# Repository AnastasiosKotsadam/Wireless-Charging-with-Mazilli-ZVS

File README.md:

# ZVS Driver with Protection

A **Mazzilli ZVS (zero-voltage switching) driver** for wireless energy transfer, built as a complete PCB with hardware overcurrent protection and an ATmega328P supervisor that monitors the oscillation, controls the startup and shows the board status on LEDs.

> **Status:** simulation (LTspice) and firmware (SimulIDE) done · schematic in KiCad in progress · PCB not yet built

---

## Features

- **Mazzilli ZVS power stage** at about **111 kHz**, powered from a **12 V DC** input
- **Soft start** that holds the MOSFET gates off at power-up
- **Hardware overcurrent protection**: shunt → current-sense amplifier → comparator → latch → gates off within microseconds, independent of the firmware
- **Two current limits** set by the ATmega: a high limit during startup (to allow the inrush current) and a normal limit during operation
- **Oscillation watchdog**: the ATmega counts the drain pulses and shuts the stage down if the frequency is missing or outside its window
- **Fault diagnosis on LEDs**: overcurrent and oscillation faults are shown separately
- **Safe by default**: the latch starts in the "off" state at power-up and after any fault, and only a button press restarts the stage

---

## How it works

```
12 V ─ Fuse ─ Shunt (5 mΩ) ─ Soft start ─ Mazzilli ZVS ─ Coupled coils ─ Rectifier ─ Load
                  │                            ▲      │
             INA181A1 (×20)                    │      │ drain signal
                  │                      gates off    │ (divider, clamp, Schmitt trigger)
             RC filter                         │      ▼
                  │                     ┌─ Fault latch ◄─── ATmega328P
             LM393 comparator ──────────┘  (74HC02)        - threshold PWM
                  ▲                                        - frequency watchdog
                  └──── threshold (PWM + RC filter) ◄──────  - LEDs, reset button
```

1. **Overcurrent:** the INA181 amplifies the voltage across the shunt. When it exceeds the threshold, the LM393 sets the latch, and two small MOSFETs pull both main gates to ground.
2. **Oscillation watchdog:** one drain is divided down, clamped and cleaned up by a Schmitt trigger, then counted by Timer1 of the ATmega. A missing or wrong frequency makes the ATmega set the latch.
3. **Startup:** the ATmega first sets the high threshold, waits for it to settle, then resets the latch. After a blanking time and a valid frequency, it switches to the normal threshold.

---

## Key parameters

| Parameter | Value |
|---|---|
| Input voltage | 12 V DC |
| Switching frequency | ~111 kHz (tank: 2 µH, 1 µF) |
| Feed chokes | 2 × 100 µH |
| Shunt | 5 mΩ |
| Current-sense amplifier | INA181A1 (gain 20, 0.1 V/A) |
| Trip current, startup | 30 A (first ~30 ms) |
| Trip current, running | 8 A |
| Frequency window | 90–130 kHz (to be confirmed by measurement) |
| Comparator | LM393, supplied from 12 V, open-collector output |
| Fault latch | 74HC02 (two NOR gates as SR latch) |
| Microcontroller | ATmega328P-PU, 16 MHz crystal, 5 V |
| Logic supply | 7805 linear regulator |

---

## LED indication

| LEDs | State |
|---|---|
| All off | Booting |
| 🟢 Green blinking | Startup, high current limit active |
| 🟢 Green steady | Running normally |
| 🔴 Red | Overcurrent trip |
| 🟡 Yellow | Oscillation fault (missing or wrong frequency) |

After a fault, the stage stays off until the **reset button** is pressed.

---

## Repository structure

```
ZVS-Driver/
├── kicad/        KiCad schematic and PCB
├── ltspice/      LTspice simulations (power stage, protection, coupling sweeps)
├── firmware/
│   └── zvs_supervisor/
│       └── zvs_supervisor.ino
├── docs/         Notes, measurements, photos
└── README.md
```

---

## Firmware

**Toolchain:** Arduino IDE 2.x with the [MiniCore](https://github.com/MCUdude/MiniCore) board package.

| Setting | Value |
|---|---|
| Board | MiniCore → ATmega328 |
| Clock | External 16 MHz |
| BOD | 4.3 V |
| Bootloader | No bootloader (programmed via ISP) |
| Programmer | Arduino as ISP |

The same code also runs unchanged on an Arduino Uno or Nano for testing.

### Pin map

| Arduino | ATmega pin | Function |
|---|---|---|
| D2 | 4 | Reset button (to GND) |
| D3 | 5 | Threshold PWM (Timer2, ~31 kHz) |
| D5 | 11 | Oscillation input (Timer1, T1) |
| D6 | 12 | Latch S (via 1N5819) |
| D7 | 13 | Latch R |
| D8 | 14 | Latch Q (read back) |
| A0 / A1 / A2 | 23 / 24 / 25 | Green / red / yellow LED |
| A3 | 26 | Current-sense output (debug) |
| D0 / D1 | 2 / 3 | Serial debug, 115200 baud |

All thresholds, timings and the frequency window are constants at the top of `zvs_supervisor.ino`.

### Programming

The board has a 6-pin ISP header (MISO, VCC, SCK, MOSI, RESET, GND). An Arduino Uno running the **ArduinoISP** example works as programmer (D10 → RESET, D11 → MOSI, D12 → MISO, D13 → SCK, plus 5 V and GND, and 10 µF between RESET and GND on the Uno).

1. Burn the fuses once: **Tools → Burn Bootloader**.
2. Upload: **Sketch → Upload Using Programmer**.

⚠️ **Program the board with the 12 V supply disconnected.** While the ATmega is being programmed it cannot supervise the power stage.

### Serial debug

A 3-pin header (GND, TX, RX) connects to a 5 V USB-UART adapter (CH340 or CP2102). TX and RX cross over, and the adapter's VCC stays unconnected.

---

## Simulation

- **LTspice:** power stage, soft start, current sensing, comparator, latch and drain sensing, with faults (shorted tank) and coupling-factor sweeps between the coils. The TI models for the INA181 and LM2903B/LM393 are available from [ti.com](https://www.ti.com) and are not included in this repository.
- **SimulIDE:** the ATmega328P running the compiled firmware, with LEDs, button, latch and a test signal on the oscillation input.

---

## Roadmap

- [x] Power stage and protection simulated in LTspice
- [x] Firmware written and tested in SimulIDE
- [ ] Finish KiCad schematic and run ERC
- [ ] Breadboard test of the control and protection circuit
- [ ] Perfboard test of the power stage with a current-limited supply
- [ ] PCB layout, revision A
- [ ] Measurements on the real board and tuning of the thresholds

---

## Safety

This circuit handles high currents, and the drain voltages reach several times the supply voltage. Test new hardware with a **current-limited lab supply**, start at low voltage, and never connect an oscilloscope ground clip to a drain. The coil and workpiece can get hot.

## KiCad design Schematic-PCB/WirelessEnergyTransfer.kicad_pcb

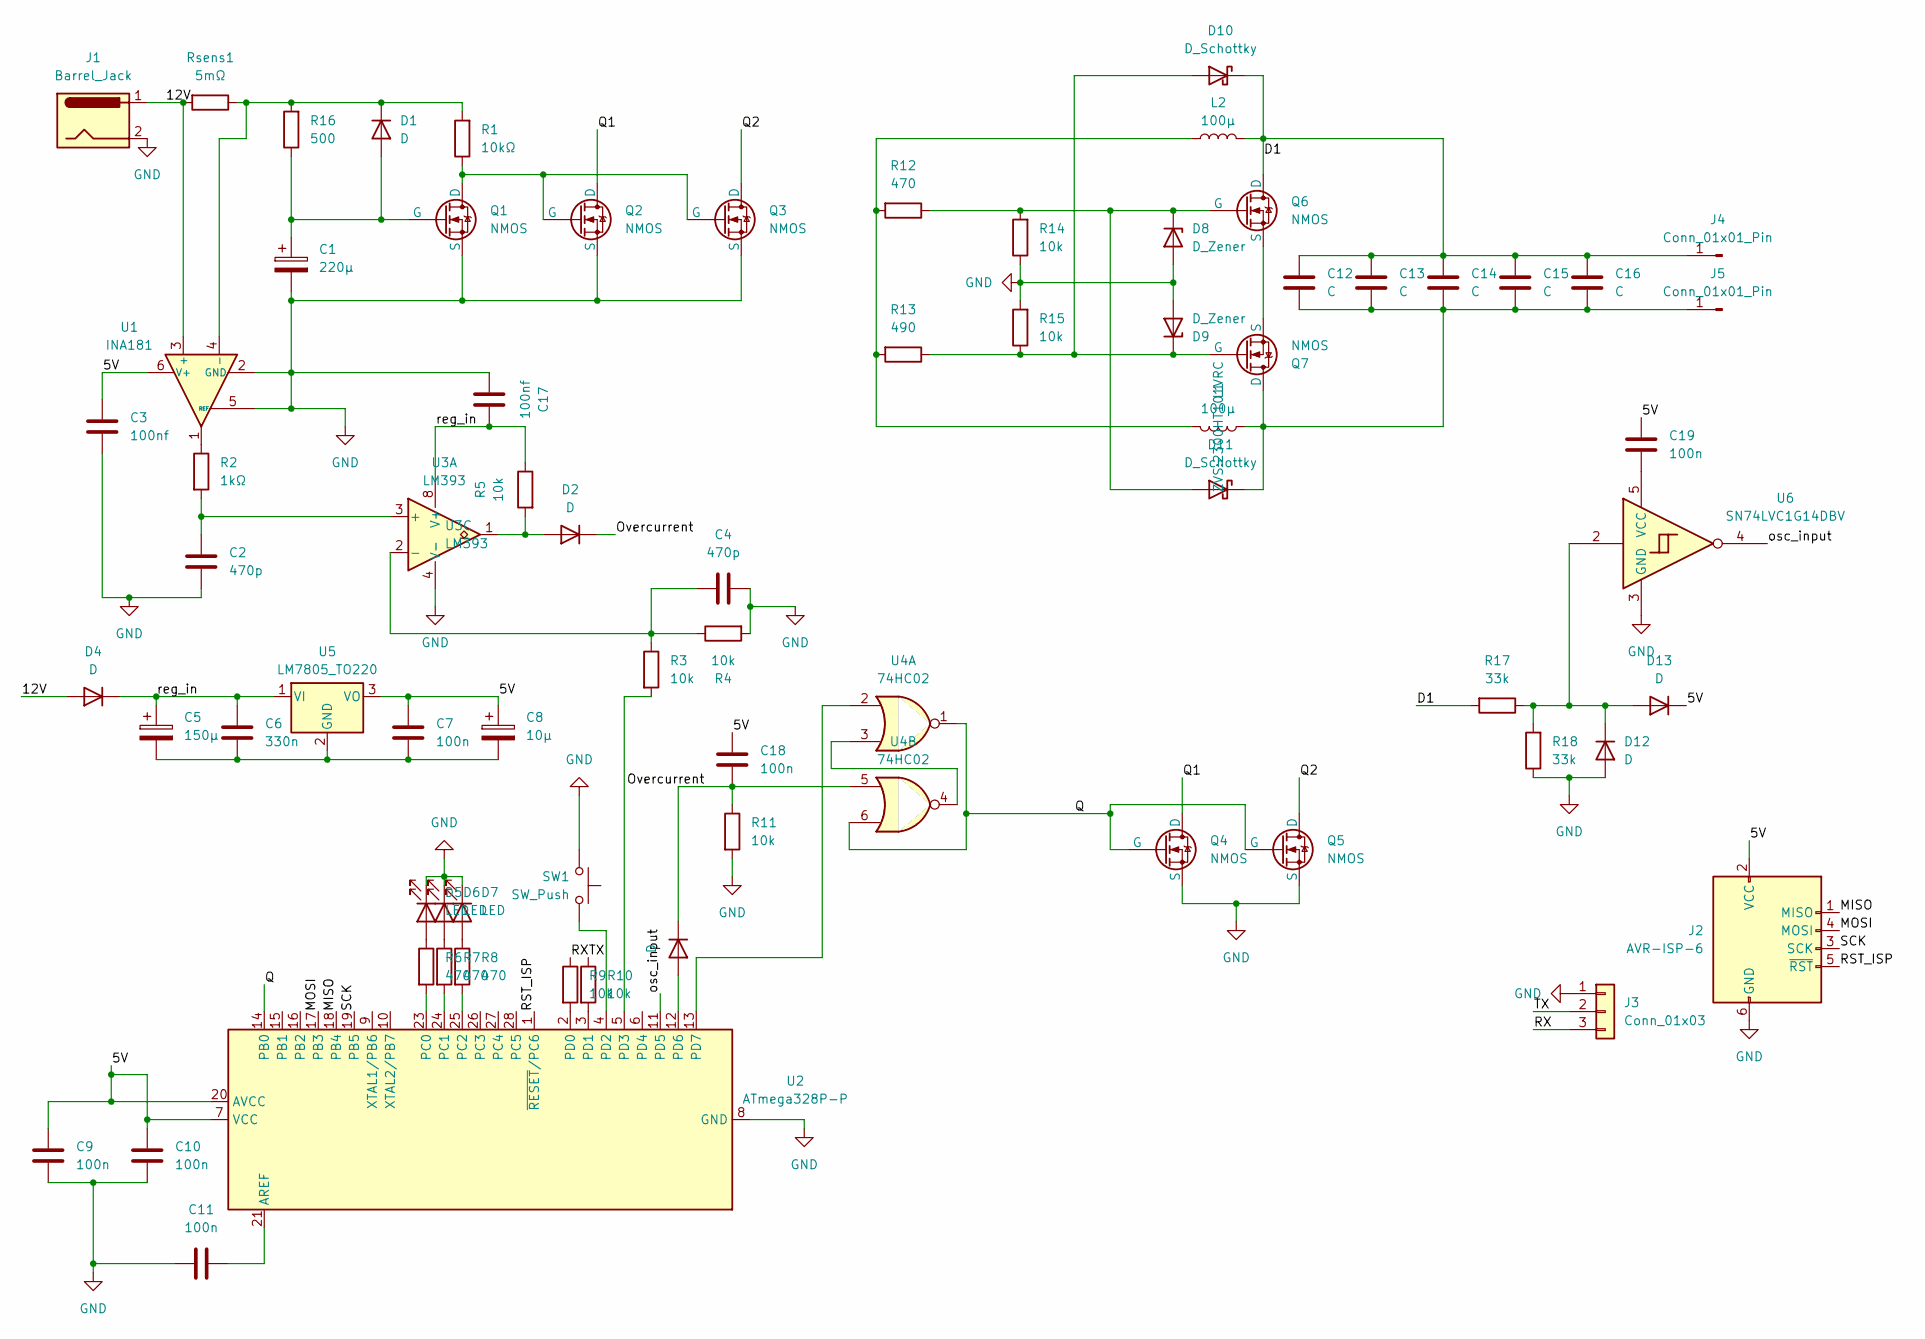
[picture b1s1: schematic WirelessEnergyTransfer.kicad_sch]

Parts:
C1: 220μ; CP_Radial_D10.0mm_P5.00mm
C2, C4: 470p; C_Axial_L5.1mm_D3.1mm_P7.50mm_Horizontal
C3, C17: 100nf; C_Disc_D10.0mm_W2.5mm_P5.00mm
C5: 150μ; CP_Radial_D10.0mm_P5.00mm
C6: 330n; C_Disc_D10.0mm_W2.5mm_P5.00mm
C7, C9, C10, C11, C18, C19: 100n; C_Disc_D10.0mm_W2.5mm_P5.00mm
C8: 10μ; CP_Radial_D10.0mm_P2.50mm_P5.00mm
C12, C13, C14, C15, C16: C; R76QR32204030J
D1, D4: D; DIOAD3020W130L900D530
D2, D3, D12, D13: D; D_DO-35_SOD27_P10.16mm_Horizontal
D5, D6, D7: LED; LED_D3.0mm_IRBlack
D8, D9: D_Zener; DIOAD1413W86L463D238
D10, D11: D_Schottky; DIOAD3020W130L900D530
J1: Barrel_Jack; BarrelJack_Horizontal
J2: AVR-ISP-6; IDC-Header_2x03_P2.54mm_Horizontal
J3: Conn_01x03; PinSocket_1x03_P2.54mm_Horizontal
J4, J5: Conn_01x01_Pin; TestPoint_Pad_4.0x4.0mm
L1, L2: 100μ; 2300HT101VRC
Q1, Q2, Q3, Q4, Q5: NMOS; 2N3904BU
Q6, Q7: NMOS; TO254P465X1028X1970-3P
R1: 10kΩ; R_Axial_DIN0309_L9.0mm_D3.2mm_P12.70mm_Horizontal
R2: 1kΩ; R_Axial_DIN0309_L9.0mm_D3.2mm_P12.70mm_Horizontal
R3, R4, R5, R9, R10, R11: 10k; R_Axial_DIN0309_L9.0mm_D3.2mm_P12.70mm_Horizontal
R6, R7, R8: 470; R_Axial_DIN0309_L9.0mm_D3.2mm_P12.70mm_Horizontal
R12: 470; R_Axial_DIN0411_L9.9mm_D3.6mm_P15.24mm_Horizontal
R13: 490; R_Axial_DIN0411_L9.9mm_D3.6mm_P15.24mm_Horizontal
R14, R15: 10k; R_Axial_DIN0411_L9.9mm_D3.6mm_P15.24mm_Horizontal
R16: 500; R_Axial_DIN0411_L9.9mm_D3.6mm_P15.24mm_Horizontal
R17, R18: 33k; R_Axial_DIN0309_L9.0mm_D3.2mm_P12.70mm_Horizontal
Rsens1: 5mΩ; R_Axial_DIN0411_L9.9mm_D3.6mm_P15.24mm_Horizontal
SW1: SW_Push; SW_CW_GPTS203211B
U1: INA181; SOT-23-6
U2: ATmega328P-P; DIP-28_W7.62mm
U3: LM393; PS8
U4: 74HC02; DIP-10_W7.62mm
U5: LM7805_TO220; TO-220-3_Vertical
U6: SN74LVC1G14DBV; SOT-23-5

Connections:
/5V: C3.1, C7.2, C8.1, C9.2, C10.2, C18.2, C19.2, D13.1 (K), J2.2 (VCC), U1.6 (V+), U2.7 (VCC), U2.20 (AVCC), U5.3 (VO)
/12V: D4.2 (A), J1.1, Rsens1.2, U1.3 (+)
/D1: C12.1, C13.1, C14.1, C15.1, C16.1, D10.1 (K), J4.1 (Pin_1_1), L2.1, Q6.1 (D), R17.2
/MISO: J2.1 (MISO), U2.18 (PB4)
/MOSI: J2.4 (MOSI), U2.17 (PB3)
/Overcurrent: C18.1, D2.1 (K), D3.1 (K), R11.1, U4.5
/Q: Q4.2 (G), Q5.2 (G), U2.14 (PB0), U4.1, U4.6
/Q1: Q2.1 (D), Q4.1 (D)
/Q2: Q3.1 (D), Q5.1 (D)
/RST_ISP: J2.5 (~RST), U2.1 (~RESET/PC6)
/RX: J3.3, R9.1
/SCK: J2.3 (SCK), U2.19 (PB5)
/TX: J3.2, R10.1
/osc_input: U2.11 (PD5), U6.4
/reg_in: C5.1, C6.2, C17.2, D4.1 (K), R5.1, U3.8 (V+), U5.1 (VI)
GND: C1.2, C2.1, C3.2, C4.1, C9.1, C10.1, C11.1, C17.1, D5.1 (K), D6.1 (K), D7.1 (K), D8.2 (A), D9.2 (A), D12.2 (A), J1.2, J2.6 (GND), J3.1, Q1.3 (S), Q2.3 (S), Q3.3 (S), Q4.3 (S), Q5.3 (S), R4.2, R11.2, R14.1, R15.2, R18.1, SW1.2, U1.2 (GND), U1.5 (REF), U2.8 (GND), U2.22 (GND), U3.4 (V-), U6.3 (GND)
unnamed: C1.1, D1.2 (A), Q1.2 (G), R16.1
unnamed: D1.1 (K), R1.2, R16.2, Rsens1.1, U1.4 (-)
unnamed: D2.2 (A), R5.2, U3.1
unnamed: D3.2 (A), U2.12 (PD6)
unnamed: D5.2 (A), R6.1
unnamed: D6.2 (A), R7.1
unnamed: D7.2 (A), R8.1
unnamed: D9.1 (K), D10.2 (A), Q7.2 (G), R13.1, R15.1
unnamed: D8.1 (K), D11.2 (A), Q6.2 (G), R12.1, R14.2
unnamed: C12.2, C13.2, C14.2, C15.2, C16.2, D11.1 (K), J5.1 (Pin_1_1), L1.1, Q7.1 (D)
unnamed: D12.1 (K), D13.2 (A), R17.1, R18.2, U6.2
unnamed: L1.2, L2.2, R12.2, R13.2
unnamed: Q1.1 (D), Q2.2 (G), Q3.2 (G), R1.1
unnamed: Q6.3 (S), Q7.3 (S)
unnamed: R2.1, U1.1
unnamed: C11.2, U2.21 (AREF)
unnamed: R6.2, U2.23 (PC0)
unnamed: R7.2, U2.24 (PC1)
unnamed: R8.2, U2.25 (PC2)
unnamed: R9.2, U2.2 (PD0)
unnamed: R10.2, U2.3 (PD1)
unnamed: SW1.1, U2.4 (PD2)
unnamed: R3.2, U2.5 (PD3)
unnamed: U2.13 (PD7), U4.2
unnamed: C2.2, R2.2, U3.3 (+)
unnamed: C4.2, R3.1, R4.1, U3.2 (-)
unnamed: U4.3, U4.4
unnamed: C5.2, C6.1, C7.1, C8.2, U5.2 (GND)
unnamed: C19.1, U6.5 (VCC)

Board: 2 copper layers, 72 parts (0 on the bottom side), 45 nets, no tracks yet.

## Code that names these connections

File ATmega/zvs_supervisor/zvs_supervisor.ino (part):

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    - Shunt 5 mOhm, INA181A1 (gain 20)

  Pin map (Arduino number / port / DIP-28 pin):
    D2  PD2 pin 4   reset button to GND (internal pull-up)
    D3  PD3 pin 5   threshold PWM (Timer2, OC2B)
    D5  PD5 pin 11  osc input (Timer1 external clock T1)
    D6  PD6 pin 12  latch S (via diode)
    D7  PD7 pin 13  latch R
    D8  PB0 pin 14  latch Q (input)
    A0  PC0 pin 23  green LED
    A1  PC1 pin 24  red LED
    A2  PC2 pin 25  yellow LED
    A3  PC3 pin 26  INA181 output (optional, debug only)
    D0/D1           serial debug (115200 baud)
*/
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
